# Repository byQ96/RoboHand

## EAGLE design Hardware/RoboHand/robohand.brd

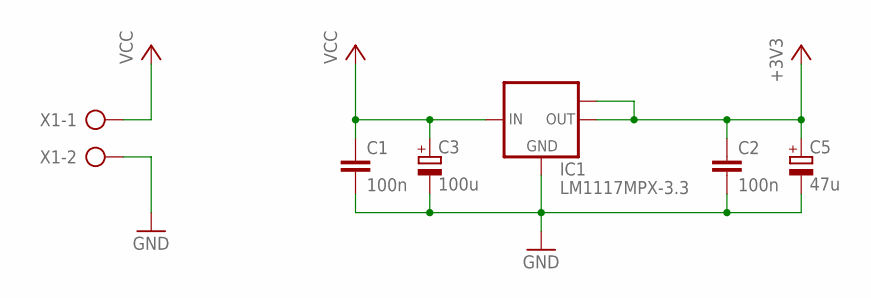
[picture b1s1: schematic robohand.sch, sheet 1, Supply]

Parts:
C1, C2: 100n; C0805
C3: 100u; CT7343
C5: 47u; CT3528
IC1: LM1117MPX-3.3; SOT223
X1: AK500/2

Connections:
+3V3: C2.1, C5.+, IC1.2 (OUT), IC1.TAB (OUT1); also elsewhere on the board
GND: C1.2, C2.2, C3.-, C5.-, IC1.1 (GND), X1.2; also elsewhere on the board
VCC: C1.1, C3.+, IC1.3 (IN), X1.1

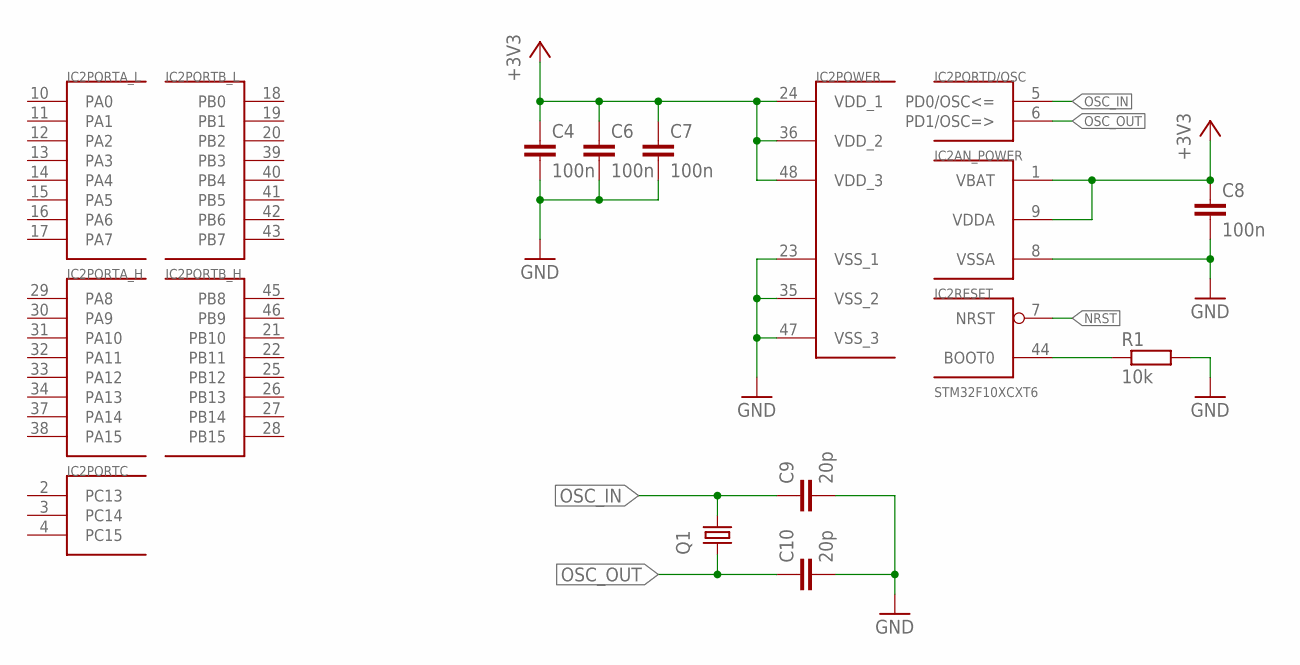
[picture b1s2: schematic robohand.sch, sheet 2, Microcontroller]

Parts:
C4, C6, C7, C8: 100n; C0805
C9, C10: 20p; C0805
IC2: STM32F10XCXT6; TQFP48
Q1: CRYSTALCTS406; CTS406
R1: 10k; R0805

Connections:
+3V3: C4.1, C6.1, C7.1, C8.1, IC2.1 (VBAT), IC2.9 (VDDA), IC2.24 (VDD_1), IC2.36 (VDD_2), IC2.48 (VDD_3); also elsewhere on the board
GND: C4.2, C6.2, C7.2, C8.2, C9.2, C10.2, IC2.8 (VSSA), IC2.23 (VSS_1), IC2.35 (VSS_2), IC2.47 (VSS_3), R1.2; also elsewhere on the board
unnamed: IC2.44 (BOOT0), R1.1
NRST: IC2.7 (NRST)
OSC_IN: C9.1, IC2.5 (PD0/OSC<=), Q1.1
OSC_OUT: C10.1, IC2.6 (PD1/OSC=>), Q1.3 (2)

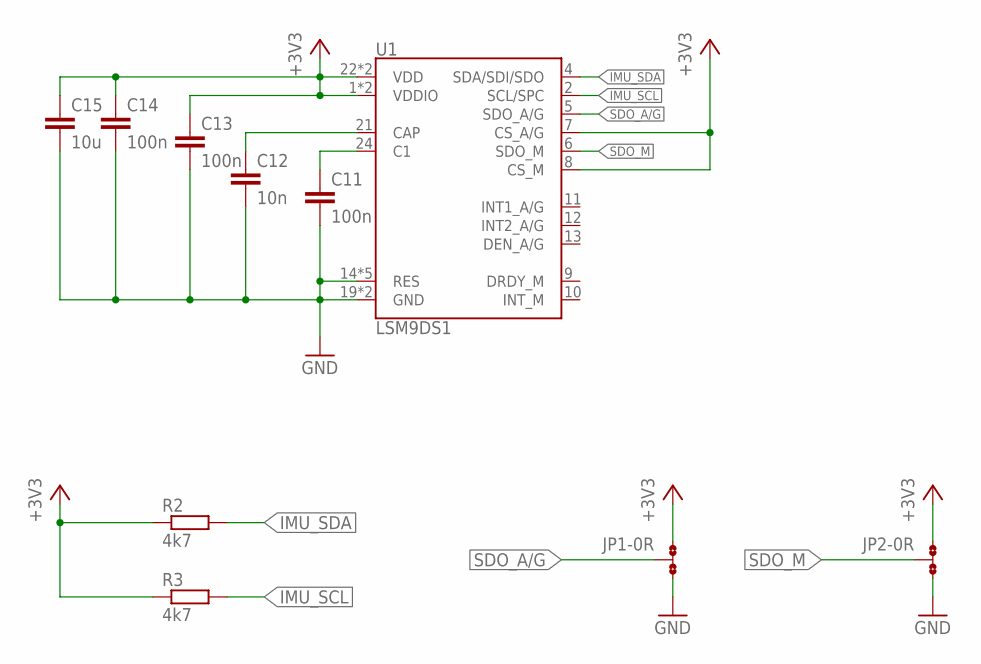
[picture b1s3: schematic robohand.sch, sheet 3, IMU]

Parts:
C11, C13, C14: 100n; C0805
C12: 10n; C0805
C15: 10u; C0805
JP1, JP2: 0R-JUMPA; A0R-JMP
R2, R3: 4k7; R0805
U1: LSM9DS1; LGA24-8X4

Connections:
+3V3: C13.1, C14.1, C15.1, JP1.1, JP2.1, R2.1, R3.1, U1.1 (VDDIO), U1.3 (VDDIO), U1.7 (CS_A/G), U1.8 (CS_M), U1.22 (VDD), U1.23 (VDD); also elsewhere on the board
GND: C11.2, C12.2, C13.2, C14.2, C15.2, JP1.3, JP2.3, U1.14 (RES), U1.15 (RES), U1.16 (RES), U1.17 (RES), U1.18 (RES), U1.19 (GND), U1.20 (GND); also elsewhere on the board
IMU_SCL: R3.2, U1.2 (SCL/SPC)
IMU_SDA: R2.2, U1.4 (SDA/SDI/SDO)
unnamed: C11.1, U1.24 (C1)
unnamed: C12.1, U1.21 (CAP)
SDO_A/G: JP1.2, U1.5 (SDO_A/G)
SDO_M: JP2.2, U1.6 (SDO_M)

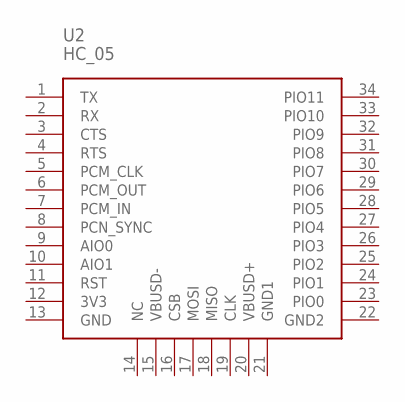
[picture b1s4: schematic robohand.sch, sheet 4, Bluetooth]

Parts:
U2: HC_05; BLUETOOTH_SMD

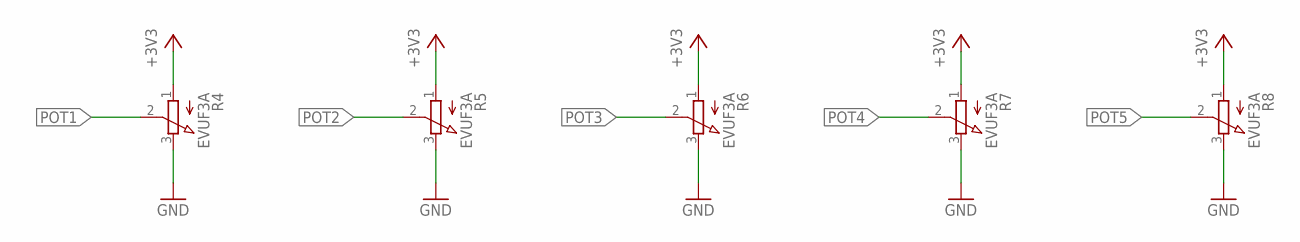
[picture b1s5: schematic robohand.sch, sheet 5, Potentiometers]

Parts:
R4, R5, R6, R7, R8: EVUF3A; EVUF

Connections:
+3V3: R4.1 (A), R5.1 (A), R6.1 (A), R7.1 (A), R8.1 (A); also elsewhere on the board
GND: R4.3 (E), R5.3 (E), R6.3 (E), R7.3 (E), R8.3 (E); also elsewhere on the board
POT1: R4.2 (S)
POT2: R5.2 (S)
POT3: R6.2 (S)
POT4: R7.2 (S)
POT5: R8.2 (S)

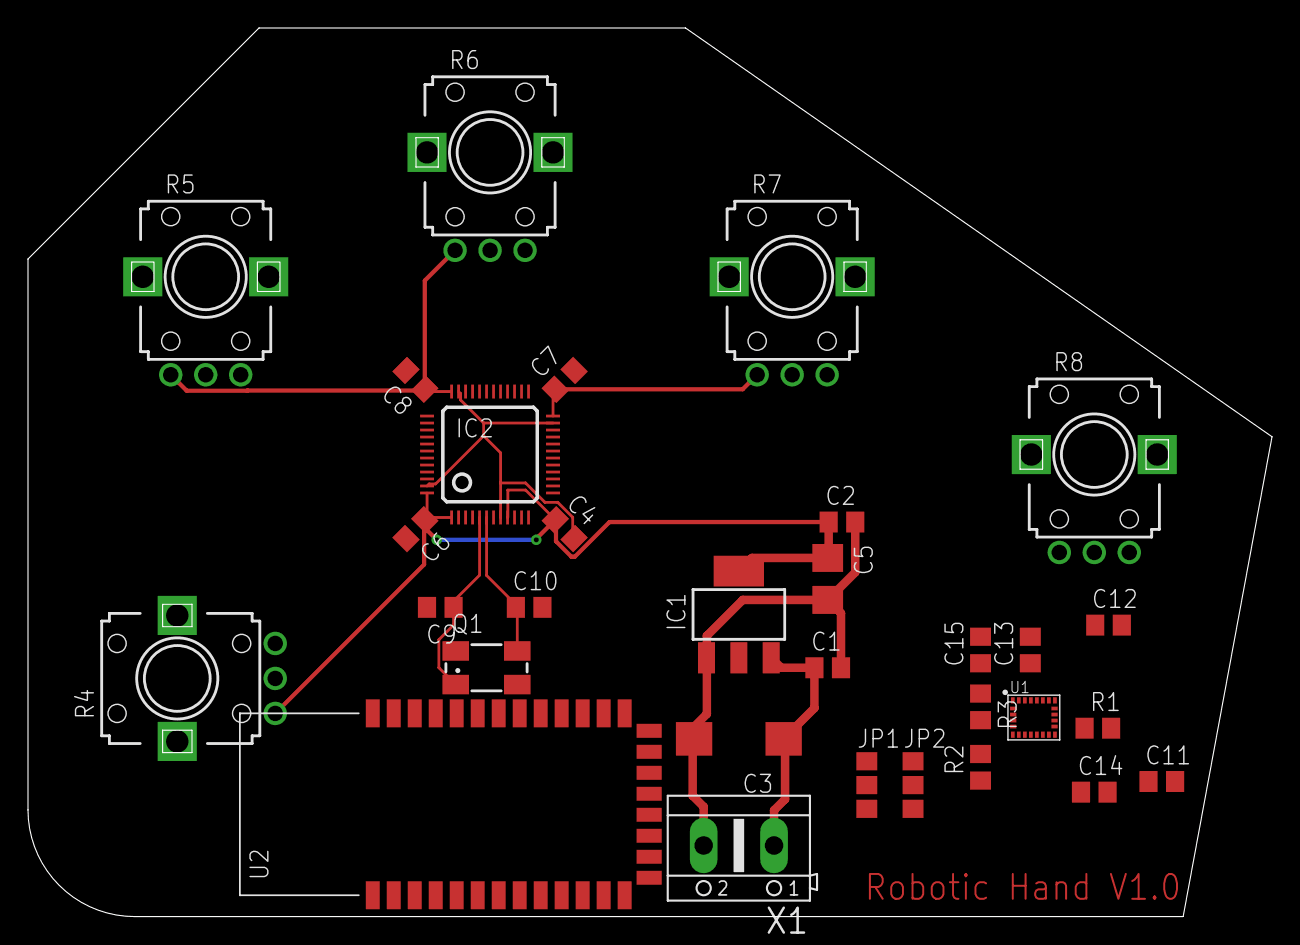
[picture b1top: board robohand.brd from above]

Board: 2 copper layers, 88.9 x 63.5 mm, 31 parts (0 on the bottom side), 12 nets.

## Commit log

2018-04-13 half scheme
2018-06-17 reainstall
